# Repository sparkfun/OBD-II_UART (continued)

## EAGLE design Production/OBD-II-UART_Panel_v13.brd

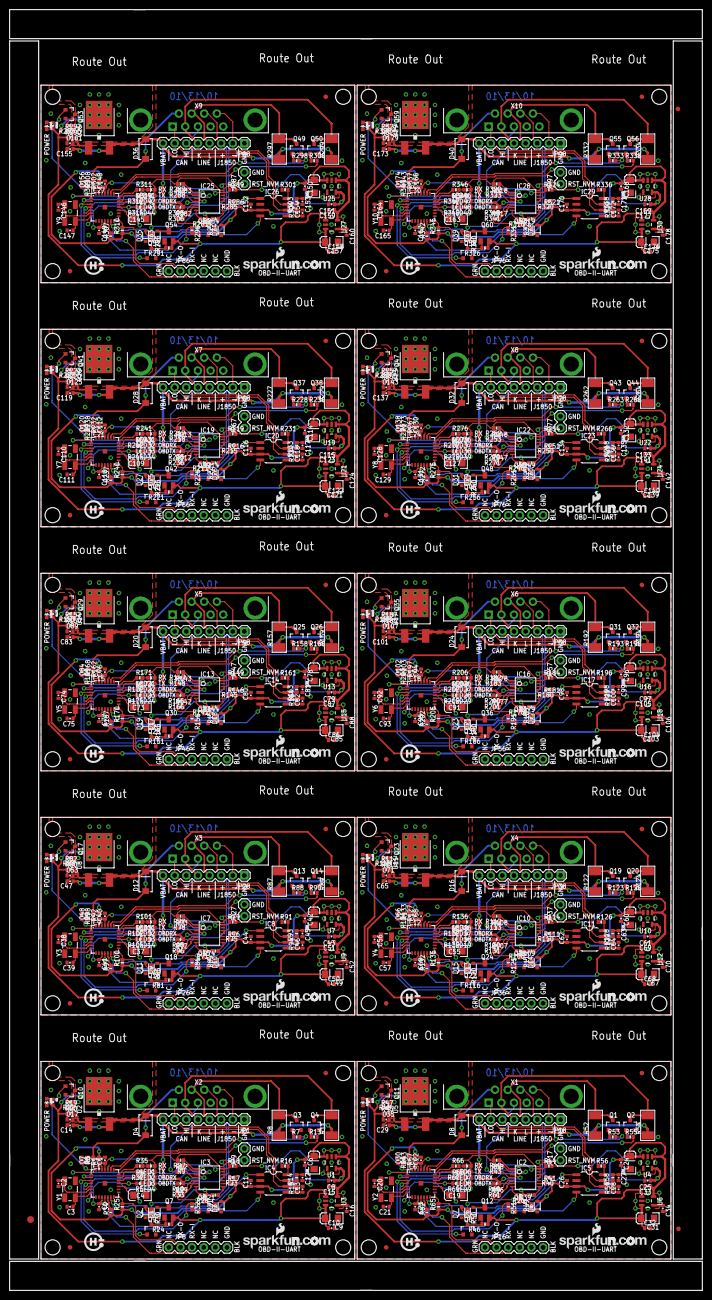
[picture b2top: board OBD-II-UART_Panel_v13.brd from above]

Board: 2 copper layers, 151.4 x 279.9 mm, 873 parts (0 on the bottom side), 570 nets.

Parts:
C1, C5, C6, C11, C17, C22, C23, C24, C26, C35, C40, C41, C42, C44, C53, C58, C59, C60, C62, C71, C76, C77, C78, C80, C89, C94, C95, C96, C98, C107, C112, C113, C114, C116, C125, C130, C131, C132, C134, C143, C148, C149, C150, C152, C161, C166, C167, C168, C170, C179: 1uF; 0402-CAP
C2, C3, C20, C21, C38, C39, C56, C57, C74, C75, C92, C93, C110, C111, C128, C129, C146, C147, C164, C165: 27pF; 0402-CAP
C4, C19, C37, C55, C73, C91, C109, C127, C145, C163: 10uF ESR<=5; EIA3216
C7, C10, C14, C29, C30, C32, C47, C48, C50, C65, C66, C68, C83, C84, C86, C101, C102, C104, C119, C120, C122, C137, C138, C140, C155, C156, C158, C173, C174, C176: 0.1uF; 0402-CAP
C8, C25, C43, C61, C79, C97, C115, C133, C151, C169: 4.7uF; 0402-CAP
C9, C18, C31, C36, C49, C54, C67, C72, C85, C90, C103, C108, C121, C126, C139, C144, C157, C162, C175, C180: 10uF; EIA3216
C12, C13, C27, C28, C45, C46, C63, C64, C81, C82, C99, C100, C117, C118, C135, C136, C153, C154, C171, C172: 560pF; 0402-CAP
C15, C33, C51, C69, C87, C105, C123, C141, C159, C177: 2.2uF; 0402-CAP
C16, C34, C52, C70, C88, C106, C124, C142, C160, C178: 470pF; 0402-CAP
D1, D2, D3, D5, D6, D7, D9, D10, D11, D13, D14, D15, D17, D18, D19, D21, D22, D23, D25, D26, D27, D29, D30, D31, D33, D34, D35, D37, D38, D39: BAS16; SOD-323
D4, D8, D12, D16, D20, D24, D28, D32, D36, D40: MBRA140; SMA-DIODE
E$1: FIDUCIAL-1.5X3
E$5, E$8: FIDUCIAL-1X2
IC1, IC6, IC9, IC12, IC15, IC18, IC21, IC24, IC27, IC30: SCANTOOL; _STN_SCANTOOL_QFN-28-S
IC2, IC3, IC7, IC10, IC13, IC16, IC19, IC22, IC25, IC28: LM339PWR; TSSOP-14
IC4, IC5, IC8, IC11, IC14, IC17, IC20, IC23, IC26, IC29: MCP2551; SO-8
JP1, JP18, JP28, JP38, JP48, JP58, JP68, JP78, JP88, JP98: 1X08
JP2, JP10, JP19, JP20, JP29, JP30, JP39, JP40, JP49, JP50, JP59, JP60, JP69, JP70, JP79, JP80, JP89, JP90, JP99, JP100: FIDUCIAL1X2; FIDUCIAL-1X2
JP3, JP11, JP21, JP31, JP41, JP51, JP61, JP71, JP81, JP91: LOGO-SFENEW; SFE-NEW-WEBLOGO
JP4, JP5, JP6, JP7, JP12, JP13, JP14, JP15, JP22, JP23, JP24, JP25, JP32, JP33, JP34, JP35, JP42, JP43, JP44, JP45, JP52, JP53, JP54, JP55, JP62, JP63, JP64, JP65, JP72, JP73, JP74, JP75, JP82, JP83, JP84, JP85, JP92, JP93, JP94, JP95: STAND-OFF
JP8, JP16, JP26, JP36, JP46, JP56, JP66, JP76, JP86, JP96: DNP; FTDI_BASIC
JP9, JP17, JP27, JP37, JP47, JP57, JP67, JP77, JP87, JP97: DNP; 1X02
LED1, LED3, LED6, LED8, LED11, LED13, LED16, LED18, LED21, LED23, LED26, LED28, LED31, LED33, LED36, LED38, LED41, LED43, LED46, LED48: YELLOW; LED-0603
LED2, LED4, LED5, LED7, LED9, LED10, LED12, LED14, LED15, LED17, LED19, LED20, LED22, LED24, LED25, LED27, LED29, LED30, LED32, LED34, LED35, LED37, LED39, LED40, LED42, LED44, LED45, LED47, LED49, LED50: RED; LED-0603
Q1, Q2, Q3, Q4, Q5, Q8, Q13, Q14, Q15, Q19, Q20, Q21, Q25, Q26, Q27, Q31, Q32, Q33, Q37, Q38, Q39, Q43, Q44, Q45, Q49, Q50, Q51, Q55, Q56, Q57: MMBT2222; SOT23-3
Q6, Q9, Q10, Q11, Q16, Q17, Q22, Q23, Q28, Q29, Q34, Q35, Q40, Q41, Q46, Q47, Q52, Q53, Q58, Q59: BSS138; SOT23-3
Q7, Q12, Q18, Q24, Q30, Q36, Q42, Q48, Q54, Q60: ZXMP6A13FTA; SOT23
R1, R9, R10, R12, R18, R21, R26, R27, R28, R29, R30, R31, R33, R36, R38, R39, R42, R43, R44, R49, R50, R57, R60, R61, R71, R72, R73, R74, R77, R78, R79, R84, R85, R92, R95, R96, R106, R107, R108, R109, R112, R113, R114, R119, R120, R127, R130, R131, R141, R142, R143, R144, R147, R148, R149, R154, R155, R162, R165, R166, R176, R177, R178, R179, R182, R183, R184, R189, R190, R197, R200, R201, R211, R212, R213, R214, R217, R218, R219, R224, R225, R232, R235, R236, R246, R247, R248, R249, R252, R253, R254, R259, R260, R267, R270, R271, R281, R282, R283, R284, R287, R288, R289, R294, R295, R302, R305, R306, R316, R317, R318, R319, R322, R323, R324, R329, R330, R337, R340, R341: 10k; 0402-RES
R2, R7, R13, R32, R51, R53, R55, R70, R86, R88, R90, R105, R121, R123, R125, R140, R156, R158, R160, R175, R191, R193, R195, R210, R226, R228, R230, R245, R261, R263, R265, R280, R296, R298, R300, R315, R331, R333, R335, R350: 1k; 0402-RES
R3, R63, R98, R133, R168, R203, R238, R273, R308, R343: 62K; 0402-RES
R4, R5, R35, R37, R66, R67, R68, R69, R101, R102, R103, R104, R136, R137, R138, R139, R171, R172, R173, R174, R206, R207, R208, R209, R241, R242, R243, R244, R276, R277, R278, R279, R311, R312, R313, R314, R346, R347, R348, R349: 330; 0402-RES
R6, R64, R99, R134, R169, R204, R239, R274, R309, R344: 10K; 0402-RES
R8, R11, R52, R54, R87, R89, R122, R124, R157, R159, R192, R194, R227, R229, R262, R264, R297, R299, R332, R334: 510 0.5W; 2010
R14, R15, R58, R59, R93, R94, R128, R129, R163, R164, R198, R199, R233, R234, R268, R269, R303, R304, R338, R339: 100; 0402-RES
R16, R23, R25, R40, R56, R65, R75, R91, R100, R110, R126, R135, R145, R161, R170, R180, R196, R205, R215, R231, R240, R250, R266, R275, R285, R301, R310, R320, R336, R345: 4.7k; 0402-RES
R17, R41, R76, R111, R146, R181, R216, R251, R286, R321: 1.2k; 0402-RES
R19, R47, R82, R117, R152, R187, R222, R257, R292, R327: 866; 0402-RES
R20, R45, R80, R115, R150, R185, R220, R255, R290, R325: 240; 0402-RES
R22, R48, R83, R118, R153, R188, R223, R258, R293, R328: 374; 0402-RES
R24, R34, R46, R62, R81, R97, R116, R132, R151, R167, R186, R202, R221, R237, R256, R272, R291, R307, R326, R342: 1.5k; 0402-RES
U1, U4, U7, U10, U13, U16, U19, U22, U25, U28: 3.3V; SOT23-5
U2, U5, U8, U11, U14, U17, U20, U23, U26, U29: V_REG_317DPACK; V-REG_DPACK
U3, U6, U9, U12, U15, U18, U21, U24, U27, U30: 5V Reg.; SOT23-5
U$1, U$2, U$3, U$4, U$5, U$6, U$7, U$8, U$9, U$14: OSHW-LOGO
X1, X2, X3, X4, X5, X6, X7, X8, X9, X10: Male DB9; DB9_MALE
Y1, Y2, Y3, Y4, Y5, Y6, Y7, Y8, Y9, Y10: 16MHz; CRYSTAL-SMD-5X3

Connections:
3.3V: C1.1, C5.1, C8.1, IC1.10, IC1.25, LED1.A, LED2.A, LED3.A, LED4.A, R9.2, R18.2, R27.2, U1.5
3.3V1: C22.1, C23.1, C25.1, IC6.10, IC6.25, LED6.A, LED7.A, LED8.A, LED9.A, R42.2, R43.2, R44.2, U4.5
3.3V2: C40.1, C41.1, C43.1, IC9.10, IC9.25, LED11.A, LED12.A, LED13.A, LED14.A, R77.2, R78.2, R79.2, U7.5
3.3V3: C58.1, C59.1, C61.1, IC12.10, IC12.25, LED16.A, LED17.A, LED18.A, LED19.A, R112.2, R113.2, R114.2, U10.5
3.3V4: C76.1, C77.1, C79.1, IC15.10, IC15.25, LED21.A, LED22.A, LED23.A, LED24.A, R147.2, R148.2, R149.2, U13.5
3.3V5: C94.1, C95.1, C97.1, IC18.10, IC18.25, LED26.A, LED27.A, LED28.A, LED29.A, R182.2, R183.2, R184.2, U16.5
3.3V6: C112.1, C113.1, C115.1, IC21.10, IC21.25, LED31.A, LED32.A, LED33.A, LED34.A, R217.2, R218.2, R219.2, U19.5
3.3V7: C130.1, C131.1, C133.1, IC24.10, IC24.25, LED36.A, LED37.A, LED38.A, LED39.A, R252.2, R253.2, R254.2, U22.5
3.3V8: C148.1, C149.1, C151.1, IC27.10, IC27.25, LED41.A, LED42.A, LED43.A, LED44.A, R287.2, R288.2, R289.2, U25.5
3.3V9: C166.1, C167.1, C169.1, IC30.10, IC30.25, LED46.A, LED47.A, LED48.A, LED49.A, R322.2, R323.2, R324.2, U28.5
5V: C6.1, C11.1, C15.1, C18.A, D3.2, IC4.3, R1.2, R17.2, R25.1, R34.1, U1.1, U1.3, U3.5
5V1: C24.1, C26.1, C33.1, C36.A, D6.2, IC5.3, R41.2, R57.2, R62.1, R65.1, U4.1, U4.3, U6.5
5V2: C42.1, C44.1, C51.1, C54.A, D10.2, IC8.3, R76.2, R92.2, R97.1, R100.1, U7.1, U7.3, U9.5
5V3: C60.1, C62.1, C69.1, C72.A, D14.2, IC11.3, R111.2, R127.2, R132.1, R135.1, U10.1, U10.3, U12.5
5V4: C78.1, C80.1, C87.1, C90.A, D18.2, IC14.3, R146.2, R162.2, R167.1, R170.1, U13.1, U13.3, U15.5
5V5: C96.1, C98.1, C105.1, C108.A, D22.2, IC17.3, R181.2, R197.2, R202.1, R205.1, U16.1, U16.3, U18.5
5V6: C114.1, C116.1, C123.1, C126.A, D26.2, IC20.3, R216.2, R232.2, R237.1, R240.1, U19.1, U19.3, U21.5
5V7: C132.1, C134.1, C141.1, C144.A, D30.2, IC23.3, R251.2, R267.2, R272.1, R275.1, U22.1, U22.3, U24.5
5V8: C150.1, C152.1, C159.1, C162.A, D34.2, IC26.3, R286.2, R302.2, R307.1, R310.1, U25.1, U25.3, U27.5
5V9: C168.1, C170.1, C177.1, C180.A, D38.2, IC29.3, R321.2, R337.2, R342.1, R345.1, U28.1, U28.3, U30.5
!ISO_K_TX: IC1.22, R13.2
!ISO_K_TX1: IC6.22, R55.2
!ISO_K_TX2: IC9.22, R90.2
!ISO_K_TX3: IC12.22, R125.2
!ISO_K_TX4: IC15.22, R160.2
!ISO_K_TX5: IC18.22, R195.2
!ISO_K_TX6: IC21.22, R230.2
!ISO_K_TX7: IC24.22, R265.2
!ISO_K_TX8: IC27.22, R300.2
!ISO_K_TX9: IC30.22, R335.2
!ISO_L_TX: IC1.23, R7.2
!ISO_L_TX1: IC6.23, R53.2
!ISO_L_TX2: IC9.23, R88.2
!ISO_L_TX3: IC12.23, R123.2
!ISO_L_TX4: IC15.23, R158.2
!ISO_L_TX5: IC18.23, R193.2
!ISO_L_TX6: IC21.23, R228.2
!ISO_L_TX7: IC24.23, R263.2
!ISO_L_TX8: IC27.23, R298.2
!ISO_L_TX9: IC30.23, R333.2
!ISO_RX: IC1.8, IC3.2, R9.1
!ISO_RX1: IC2.2, IC6.8, R43.1
!ISO_RX2: IC7.2, IC9.8, R78.1
!ISO_RX3: IC10.2, IC12.8, R113.1
!ISO_RX4: IC13.2, IC15.8, R148.1
!ISO_RX5: IC16.2, IC18.8, R183.1
!ISO_RX6: IC19.2, IC21.8, R218.1
!ISO_RX7: IC22.2, IC24.8, R253.1
!ISO_RX8: IC25.2, IC27.8, R288.1
!ISO_RX9: IC28.2, IC30.8, R323.1
!OBD_RX_STATUS!/PGC: IC1.19, R4.1
!OBD_RX_STATUS!/PGC1: IC6.19, R68.1
!OBD_RX_STATUS!/PGC2: IC9.19, R103.1
!OBD_RX_STATUS!/PGC3: IC12.19, R138.1
!OBD_RX_STATUS!/PGC4: IC15.19, R173.1
!OBD_RX_STATUS!/PGC5: IC18.19, R208.1
!OBD_RX_STATUS!/PGC6: IC21.19, R243.1
!OBD_RX_STATUS!/PGC7: IC24.19, R278.1
!OBD_RX_STATUS!/PGC8: IC27.19, R313.1
!OBD_RX_STATUS!/PGC9: IC30.19, R348.1
!VPW_RX: IC1.1, IC3.14, R18.1
!VPW_RX1: IC2.14, IC6.1, R44.1
!VPW_RX2: IC7.14, IC9.1, R79.1
!VPW_RX3: IC10.14, IC12.1, R114.1
!VPW_RX4: IC13.14, IC15.1, R149.1
!VPW_RX5: IC16.14, IC18.1, R184.1
!VPW_RX6: IC19.14, IC21.1, R219.1
!VPW_RX7: IC22.14, IC24.1, R254.1
!VPW_RX8: IC25.14, IC27.1, R289.1
!VPW_RX9: IC28.14, IC30.1, R324.1
BATT_V: C7.1, IC1.27, R3.1, R6.2
BATT_V1: C30.1, IC6.27, R63.1, R64.2
BATT_V2: C48.1, IC9.27, R98.1, R99.2
BATT_V3: C66.1, IC12.27, R133.1, R134.2
BATT_V4: C84.1, IC15.27, R168.1, R169.2
BATT_V5: C102.1, IC18.27, R203.1, R204.2
BATT_V6: C120.1, IC21.27, R238.1, R239.2
BATT_V7: C138.1, IC24.27, R273.1, R274.2
BATT_V8: C156.1, IC27.27, R308.1, R309.2
BATT_V9: C174.1, IC30.27, R343.1, R344.2
CAN_HI: IC4.7, JP1.6, R14.2, X2.3
CAN_HI1: IC5.7, JP18.6, R58.2, X1.3
CAN_HI2: IC8.7, JP28.6, R93.2, X3.3
CAN_HI3: IC11.7, JP38.6, R128.2, X4.3
CAN_HI4: IC14.7, JP48.6, R163.2, X5.3
CAN_HI5: IC17.7, JP58.6, R198.2, X6.3
CAN_HI6: IC20.7, JP68.6, R233.2, X7.3
CAN_HI7: IC23.7, JP78.6, R268.2, X8.3
CAN_HI8: IC26.7, JP88.6, R303.2, X9.3
CAN_HI9: IC29.7, JP98.6, R338.2, X10.3
CAN_LO: IC4.6, JP1.7, R15.2, X2.5
CAN_LO1: IC5.6, JP18.7, R59.2, X1.5
CAN_LO2: IC8.6, JP28.7, R94.2, X3.5
CAN_LO3: IC11.6, JP38.7, R129.2, X4.5
CAN_LO4: IC14.6, JP48.7, R164.2, X5.5
CAN_LO5: IC17.6, JP58.7, R199.2, X6.5
CAN_LO6: IC20.6, JP68.7, R234.2, X7.5
CAN_LO7: IC23.6, JP78.7, R269.2, X8.5
CAN_LO8: IC26.6, JP88.7, R304.2, X9.5
CAN_LO9: IC29.6, JP98.7, R339.2, X10.5
CAN_RX: IC1.11, IC4.4
CAN_RX1: IC5.4, IC6.11
CAN_RX2: IC8.4, IC9.11
CAN_RX3: IC11.4, IC12.11
CAN_RX4: IC14.4, IC15.11
CAN_RX5: IC17.4, IC18.11
CAN_RX6: IC20.4, IC21.11
CAN_RX7: IC23.4, IC24.11
CAN_RX8: IC26.4, IC27.11
CAN_RX9: IC29.4, IC30.11
CAN_TX: IC1.12, IC4.1, R34.2
CAN_TX1: IC5.1, IC6.12, R62.2
CAN_TX2: IC8.1, IC9.12, R97.2
CAN_TX3: IC11.1, IC12.12, R132.2
CAN_TX4: IC14.1, IC15.12, R167.2
CAN_TX5: IC17.1, IC18.12, R202.2
CAN_TX6: IC20.1, IC21.12, R237.2
CAN_TX7: IC23.1, IC24.12, R272.2
CAN_TX8: IC26.1, IC27.12, R307.2
CAN_TX9: IC29.1, IC30.12, R342.2
GND: C1.2, C2.2, C3.2, C4.C, C5.2, C6.2, C7.2, C8.2, C9.C, C10.2, C11.2, C12.2, C13.2, C14.2, C15.2, C16.2, C17.2, C18.C, D2.1, IC1.5, IC1.16, IC1.24, IC1.EXP, IC3.12, IC4.2, JP1.1, JP8.GND, JP9.2, LED5.C, Q3.2, Q4.2, Q8.2, Q9.2, Q10.2, R6.1, R16.1, R22.1, R23.1, R33.2, U1.2, U3.2, X2.1, X2.2
GND1: C19.C, C20.2, C21.2, C22.2, C23.2, C24.2, C25.2, C26.2, C27.2, C28.2, C29.2, C30.2, C31.C, C32.2, C33.2, C34.2, C35.2, C36.C, D7.1, IC2.12, IC5.2, IC6.5, IC6.16, IC6.24, IC6.EXP, JP16.GND, JP17.2, JP18.1, LED10.C, Q1.2, Q2.2, Q5.2, Q6.2, Q11.2, R40.1, R48.1, R56.1, R61.2, R64.1, U4.2, U6.2, X1.1, X1.2
GND2: C37.C, C38.2, C39.2, C40.2, C41.2, C42.2, C43.2, C44.2, C45.2, C46.2, C47.2, C48.2, C49.C, C50.2, C51.2, C52.2, C53.2, C54.C, D11.1, IC7.12, IC8.2, IC9.5, IC9.16, IC9.24, IC9.EXP, JP26.GND, JP27.2, JP28.1, LED15.C, Q13.2, Q14.2, Q15.2, Q16.2, Q17.2, R75.1, R83.1, R91.1, R96.2, R99.1, U7.2, U9.2, X3.1, X3.2
GND3: C55.C, C56.2, C57.2, C58.2, C59.2, C60.2, C61.2, C62.2, C63.2, C64.2, C65.2, C66.2, C67.C, C68.2, C69.2, C70.2, C71.2, C72.C, D15.1, IC10.12, IC11.2, IC12.5, IC12.16, IC12.24, IC12.EXP, JP36.GND, JP37.2, JP38.1, LED20.C, Q19.2, Q20.2, Q21.2, Q22.2, Q23.2, R110.1, R118.1, R126.1, R131.2, R134.1, U10.2, U12.2, X4.1, X4.2
GND4: C73.C, C74.2, C75.2, C76.2, C77.2, C78.2, C79.2, C80.2, C81.2, C82.2, C83.2, C84.2, C85.C, C86.2, C87.2, C88.2, C89.2, C90.C, D19.1, IC13.12, IC14.2, IC15.5, IC15.16, IC15.24, IC15.EXP, JP46.GND, JP47.2, JP48.1, LED25.C, Q25.2, Q26.2, Q27.2, Q28.2, Q29.2, R145.1, R153.1, R161.1, R166.2, R169.1, U13.2, U15.2, X5.1, X5.2
GND5: C91.C, C92.2, C93.2, C94.2, C95.2, C96.2, C97.2, C98.2, C99.2, C100.2, C101.2, C102.2, C103.C, C104.2, C105.2, C106.2, C107.2, C108.C, D23.1, IC16.12, IC17.2, IC18.5, IC18.16, IC18.24, IC18.EXP, JP56.GND, JP57.2, JP58.1, LED30.C, Q31.2, Q32.2, Q33.2, Q34.2, Q35.2, R180.1, R188.1, R196.1, R201.2, R204.1, U16.2, U18.2, X6.1, X6.2
GND6: C109.C, C110.2, C111.2, C112.2, C113.2, C114.2, C115.2, C116.2, C117.2, C118.2, C119.2, C120.2, C121.C, C122.2, C123.2, C124.2, C125.2, C126.C, D27.1, IC19.12, IC20.2, IC21.5, IC21.16, IC21.24, IC21.EXP, JP66.GND, JP67.2, JP68.1, LED35.C, Q37.2, Q38.2, Q39.2, Q40.2, Q41.2, R215.1, R223.1, R231.1, R236.2, R239.1, U19.2, U21.2, X7.1, X7.2
GND7: C127.C, C128.2, C129.2, C130.2, C131.2, C132.2, C133.2, C134.2, C135.2, C136.2, C137.2, C138.2, C139.C, C140.2, C141.2, C142.2, C143.2, C144.C, D31.1, IC22.12, IC23.2, IC24.5, IC24.16, IC24.24, IC24.EXP, JP76.GND, JP77.2, JP78.1, LED40.C, Q43.2, Q44.2, Q45.2, Q46.2, Q47.2, R250.1, R258.1, R266.1, R271.2, R274.1, U22.2, U24.2, X8.1, X8.2
GND8: C145.C, C146.2, C147.2, C148.2, C149.2, C150.2, C151.2, C152.2, C153.2, C154.2, C155.2, C156.2, C157.C, C158.2, C159.2, C160.2, C161.2, C162.C, D35.1, IC25.12, IC26.2, IC27.5, IC27.16, IC27.24, IC27.EXP, JP86.GND, JP87.2, JP88.1, LED45.C, Q49.2, Q50.2, Q51.2, Q52.2, Q53.2, R285.1, R293.1, R301.1, R306.2, R309.1, U25.2, U27.2, X9.1, X9.2
GND9: C163.C, C164.2, C165.2, C166.2, C167.2, C168.2, C169.2, C170.2, C171.2, C172.2, C173.2, C174.2, C175.C, C176.2, C177.2, C178.2, C179.2, C180.C, D39.1, IC28.12, IC29.2, IC30.5, IC30.16, IC30.24, IC30.EXP, JP96.GND, JP97.2, JP98.1, LED50.C, Q55.2, Q56.2, Q57.2, Q58.2, Q59.2, R320.1, R328.1, R336.1, R341.2, R344.1, U28.2, U30.2, X10.1, X10.2
J1850BUS+: D1.1, JP1.3, R21.1, R28.1, R30.1, X2.7
J1850BUS+1: D5.1, JP18.3, R26.1, R39.1, R50.1, X1.7
J1850BUS+2: D9.1, JP28.3, R71.1, R74.1, R85.1, X3.7
J1850BUS+3: D13.1, JP38.3, R106.1, R109.1, R120.1, X4.7
J1850BUS+4: D17.1, JP48.3, R141.1, R144.1, R155.1, X5.7
J1850BUS+5: D21.1, JP58.3, R176.1, R179.1, R190.1, X6.7
J1850BUS+6: D25.1, JP68.3, R211.1, R214.1, R225.1, X7.7
J1850BUS+7: D29.1, JP78.3, R246.1, R249.1, R260.1, X8.7
J1850BUS+8: D33.1, JP88.3, R281.1, R284.1, R295.1, X9.7
J1850BUS+9: D37.1, JP98.3, R316.1, R319.1, R330.1, X10.7
J1850BUS+_TX: IC1.3, Q9.1
J1850BUS+_TX1: IC6.3, Q6.1
J1850BUS+_TX2: IC9.3, Q16.1
J1850BUS+_TX3: IC12.3, Q22.1
J1850BUS+_TX4: IC15.3, Q28.1
J1850BUS+_TX5: IC18.3, Q34.1
J1850BUS+_TX6: IC21.3, Q40.1
J1850BUS+_TX7: IC24.3, Q46.1
J1850BUS+_TX8: IC27.3, Q52.1
J1850BUS+_TX9: IC30.3, Q58.1
J1850BUS-: JP1.2, Q8.3, R29.1, R31.2, X2.6
J1850BUS-1: JP18.2, Q5.3, R36.1, R49.2, X1.6
J1850BUS-2: JP28.2, Q15.3, R72.1, R84.2, X3.6
J1850BUS-3: JP38.2, Q21.3, R107.1, R119.2, X4.6
J1850BUS-4: JP48.2, Q27.3, R142.1, R154.2, X5.6
J1850BUS-5: JP58.2, Q33.3, R177.1, R189.2, X6.6
J1850BUS-6: JP68.2, Q39.3, R212.1, R224.2, X7.6
J1850BUS-7: JP78.2, Q45.3, R247.1, R259.2, X8.6
J1850BUS-8: JP88.2, Q51.3, R282.1, R294.2, X9.6
J1850BUS-9: JP98.2, Q57.3, R317.1, R329.2, X10.6
J1850BUS-_TX: IC1.4, R32.1
J1850BUS-_TX1: IC6.4, R51.1
J1850BUS-_TX2: IC9.4, R86.1
J1850BUS-_TX3: IC12.4, R121.1
J1850BUS-_TX4: IC15.4, R156.1
J1850BUS-_TX5: IC18.4, R191.1
J1850BUS-_TX6: IC21.4, R226.1
J1850BUS-_TX7: IC24.4, R261.1
J1850BUS-_TX8: IC27.4, R296.1
J1850BUS-_TX9: IC30.4, R331.1
K-LINE: JP1.5, Q4.3, R11.2, R12.1, X2.4
K-LINE1: JP18.5, Q2.3, R38.1, R54.2, X1.4
K-LINE2: JP28.5, Q14.3, R73.1, R89.2, X3.4
K-LINE3: JP38.5, Q20.3, R108.1, R124.2, X4.4
K-LINE4: JP48.5, Q26.3, R143.1, R159.2, X5.4
K-LINE5: JP58.5, Q32.3, R178.1, R194.2, X6.4
K-LINE6: JP68.5, Q38.3, R213.1, R229.2, X7.4
K-LINE7: JP78.5, Q44.3, R248.1, R264.2, X8.4
K-LINE8: JP88.5, Q50.3, R283.1, R299.2, X9.4
K-LINE9: JP98.5, Q56.3, R318.1, R334.2, X10.4
L-LINE: JP1.4, Q3.3, R8.2, X2.8
L-LINE1: JP18.4, Q1.3, R52.2, X1.8
L-LINE2: JP28.4, Q13.3, R87.2, X3.8
L-LINE3: JP38.4, Q19.3, R122.2, X4.8
L-LINE4: JP48.4, Q25.3, R157.2, X5.8
L-LINE5: JP58.4, Q31.3, R192.2, X6.8
L-LINE6: JP68.4, Q37.3, R227.2, X7.8
L-LINE7: JP78.4, Q43.3, R262.2, X8.8
L-LINE8: JP88.4, Q49.3, R297.2, X9.8
L-LINE9: JP98.4, Q55.3, R332.2, X10.8
unnamed: IC3.7, R28.2
unnamed: C19.A, IC6.17
unnamed: IC3.6, R29.2
unnamed: Q4.1, R13.1
unnamed: Q3.1, R7.1
unnamed: IC3.5, R10.2, R33.1
unnamed: IC3.8, R21.2
unnamed: R19.2, R20.2, U2.1
unnamed: D1.2, Q7.3
unnamed: C12.1, R14.1
unnamed: IC4.8, R16.2
unnamed: IC3.9, R17.1, R23.2
unnamed: IC3.4, R12.2
unnamed: D3.1, R31.1
unnamed: IC2.7, R26.2
unnamed: IC2.6, R36.2
unnamed: IC2.9, R40.2, R41.1
unnamed: Q7.1, Q9.3, R24.2
unnamed: D6.1, R49.1
unnamed: Q6.3, Q12.1, R46.2
unnamed: Q11.3, R47.1, R48.2
unnamed: Q10.3, R19.1, R22.2
unnamed: D7.2, R50.2
unnamed: D2.2, R30.2
unnamed: Q8.1, R32.2
unnamed: C4.A, IC1.17
unnamed: C13.1, R15.1
unnamed: Q5.1, R51.2
unnamed: Q2.1, R55.1
unnamed: LED3.C, R4.2
unnamed: LED4.C, R5.1
unnamed: LED5.A, R2.1
unnamed: Q1.1, R53.1
unnamed: C16.1, U3.4
unnamed: LED1.C, R35.2
unnamed: LED2.C, R37.1
unnamed: IC5.8, R56.2
unnamed: C27.1, R58.1
unnamed: C28.1, R59.1
unnamed: R45.2, R47.2, U5.1
unnamed: IC2.5, R60.2, R61.1
unnamed: IC2.4, R38.2
unnamed: IC2.8, R39.2
unnamed: D5.2, Q12.3
unnamed: LED6.C, R66.2
unnamed: LED7.C, R67.1
unnamed: LED8.C, R68.2
unnamed: LED9.C, R69.1
unnamed: C34.1, U6.4
unnamed: LED10.A, R70.1
unnamed: C37.A, IC9.17
unnamed: IC7.7, R71.2
unnamed: IC7.6, R72.2
unnamed: IC7.9, R75.2, R76.1
unnamed: D10.1, R84.1
unnamed: Q16.3, Q18.1, R81.2
unnamed: Q17.3, R82.1, R83.2
unnamed: D11.2, R85.2
unnamed: Q15.1, R86.2
unnamed: Q14.1, R90.1
unnamed: Q13.1, R88.1
unnamed: IC8.8, R91.2
unnamed: C45.1, R93.1
unnamed: C46.1, R94.1
unnamed: R80.2, R82.2, U8.1
unnamed: IC7.5, R95.2, R96.1
unnamed: IC7.4, R73.2
unnamed: IC7.8, R74.2
unnamed: D9.2, Q18.3
unnamed: LED11.C, R101.2
unnamed: LED12.C, R102.1
unnamed: LED13.C, R103.2
unnamed: LED14.C, R104.1
unnamed: C52.1, U9.4
unnamed: LED15.A, R105.1
unnamed: C55.A, IC12.17
unnamed: IC10.7, R106.2
unnamed: IC10.6, R107.2
unnamed: IC10.9, R110.2, R111.1
unnamed: D14.1, R119.1
unnamed: Q22.3, Q24.1, R116.2
unnamed: Q23.3, R117.1, R118.2
unnamed: D15.2, R120.2
unnamed: Q21.1, R121.2
unnamed: Q20.1, R125.1
unnamed: Q19.1, R123.1
unnamed: IC11.8, R126.2
unnamed: C63.1, R128.1
unnamed: C64.1, R129.1
unnamed: R115.2, R117.2, U11.1
unnamed: IC10.5, R130.2, R131.1
unnamed: IC10.4, R108.2
unnamed: IC10.8, R109.2
unnamed: D13.2, Q24.3
unnamed: LED16.C, R136.2
unnamed: LED17.C, R137.1
unnamed: LED18.C, R138.2
unnamed: LED19.C, R139.1
unnamed: C70.1, U12.4
unnamed: LED20.A, R140.1
unnamed: C73.A, IC15.17
unnamed: IC13.7, R141.2
unnamed: IC13.6, R142.2
unnamed: IC13.9, R145.2, R146.1
unnamed: D18.1, R154.1
unnamed: Q28.3, Q30.1, R151.2
unnamed: Q29.3, R152.1, R153.2
unnamed: D19.2, R155.2
unnamed: Q27.1, R156.2
unnamed: Q26.1, R160.1
unnamed: Q25.1, R158.1
unnamed: IC14.8, R161.2
unnamed: C81.1, R163.1
unnamed: C82.1, R164.1
unnamed: R150.2, R152.2, U14.1
unnamed: IC13.5, R165.2, R166.1
unnamed: IC13.4, R143.2
unnamed: IC13.8, R144.2
unnamed: D17.2, Q30.3
unnamed: LED21.C, R171.2
unnamed: LED22.C, R172.1
unnamed: LED23.C, R173.2
unnamed: LED24.C, R174.1
unnamed: C88.1, U15.4
unnamed: LED25.A, R175.1
unnamed: C91.A, IC18.17
unnamed: IC16.7, R176.2
unnamed: IC16.6, R177.2
unnamed: IC16.9, R180.2, R181.1
unnamed: D22.1, R189.1
unnamed: Q34.3, Q36.1, R186.2
unnamed: Q35.3, R187.1, R188.2
unnamed: D23.2, R190.2
unnamed: Q33.1, R191.2
unnamed: Q32.1, R195.1
unnamed: Q31.1, R193.1
unnamed: IC17.8, R196.2
unnamed: C99.1, R198.1
unnamed: C100.1, R199.1
unnamed: R185.2, R187.2, U17.1
unnamed: IC16.5, R200.2, R201.1
unnamed: IC16.4, R178.2
unnamed: IC16.8, R179.2
unnamed: D21.2, Q36.3
unnamed: LED26.C, R206.2
unnamed: LED27.C, R207.1
unnamed: LED28.C, R208.2
unnamed: LED29.C, R209.1
unnamed: C106.1, U18.4
unnamed: LED30.A, R210.1
unnamed: C109.A, IC21.17
unnamed: IC19.7, R211.2
unnamed: IC19.6, R212.2
unnamed: IC19.9, R215.2, R216.1
unnamed: D26.1, R224.1
unnamed: Q40.3, Q42.1, R221.2
unnamed: Q41.3, R222.1, R223.2
unnamed: D27.2, R225.2
unnamed: Q39.1, R226.2
unnamed: Q38.1, R230.1
unnamed: Q37.1, R228.1
unnamed: IC20.8, R231.2
unnamed: C117.1, R233.1
unnamed: C118.1, R234.1
unnamed: R220.2, R222.2, U20.1
unnamed: IC19.5, R235.2, R236.1
unnamed: IC19.4, R213.2
unnamed: IC19.8, R214.2
unnamed: D25.2, Q42.3
unnamed: LED31.C, R241.2
unnamed: LED32.C, R242.1
unnamed: LED33.C, R243.2
unnamed: LED34.C, R244.1
unnamed: C124.1, U21.4
unnamed: LED35.A, R245.1
unnamed: C127.A, IC24.17
unnamed: IC22.7, R246.2
unnamed: IC22.6, R247.2
unnamed: IC22.9, R250.2, R251.1
unnamed: D30.1, R259.1
unnamed: Q46.3, Q48.1, R256.2
unnamed: Q47.3, R257.1, R258.2
unnamed: D31.2, R260.2
unnamed: Q45.1, R261.2
unnamed: Q44.1, R265.1
unnamed: Q43.1, R263.1
unnamed: IC23.8, R266.2
unnamed: C135.1, R268.1
unnamed: C136.1, R269.1
unnamed: R255.2, R257.2, U23.1
unnamed: IC22.5, R270.2, R271.1
unnamed: IC22.4, R248.2
unnamed: IC22.8, R249.2
unnamed: D29.2, Q48.3
unnamed: LED36.C, R276.2
unnamed: LED37.C, R277.1
unnamed: LED38.C, R278.2
unnamed: LED39.C, R279.1
unnamed: C142.1, U24.4
unnamed: LED40.A, R280.1
unnamed: C145.A, IC27.17
unnamed: IC25.7, R281.2
unnamed: IC25.6, R282.2
unnamed: IC25.9, R285.2, R286.1
unnamed: D34.1, R294.1
unnamed: Q52.3, Q54.1, R291.2
unnamed: Q53.3, R292.1, R293.2
unnamed: D35.2, R295.2
unnamed: Q51.1, R296.2
unnamed: Q50.1, R300.1
unnamed: Q49.1, R298.1
unnamed: IC26.8, R301.2
unnamed: C153.1, R303.1
unnamed: C154.1, R304.1
unnamed: R290.2, R292.2, U26.1
unnamed: IC25.5, R305.2, R306.1
unnamed: IC25.4, R283.2
unnamed: IC25.8, R284.2
unnamed: D33.2, Q54.3
unnamed: LED41.C, R311.2
unnamed: LED42.C, R312.1
unnamed: LED43.C, R313.2
unnamed: LED44.C, R314.1
unnamed: C160.1, U27.4
unnamed: LED45.A, R315.1
unnamed: C163.A, IC30.17
unnamed: IC28.7, R316.2
unnamed: IC28.6, R317.2
unnamed: IC28.9, R320.2, R321.1
unnamed: D38.1, R329.1
unnamed: Q58.3, Q60.1, R326.2
unnamed: Q59.3, R327.1, R328.2
unnamed: D39.2, R330.2
unnamed: Q57.1, R331.2
unnamed: Q56.1, R335.1
unnamed: Q55.1, R333.1
unnamed: IC29.8, R336.2
unnamed: C171.1, R338.1
unnamed: C172.1, R339.1
unnamed: R325.2, R327.2, U29.1
unnamed: IC28.5, R340.2, R341.1
unnamed: IC28.4, R318.2
unnamed: IC28.8, R319.2
unnamed: D37.2, Q60.3
unnamed: LED46.C, R346.2
unnamed: LED47.C, R347.1
unnamed: LED48.C, R348.2
unnamed: LED49.C, R349.1
unnamed: C178.1, U30.4
unnamed: LED50.A, R350.1
OSC1: C2.1, IC1.6, Y1.3
OSC2: C3.1, IC1.7, Y1.1
OSC3: C20.1, IC6.6, Y2.3
OSC4: C21.1, IC6.7, Y2.1
OSC5: C38.1, IC9.6, Y3.3
OSC6: C39.1, IC9.7, Y3.1
OSC7: C56.1, IC12.6, Y4.3
OSC8: C57.1, IC12.7, Y4.1
OSC9: C74.1, IC15.6, Y5.3
OSC10: C75.1, IC15.7, Y5.1
OSC11: C92.1, IC18.6, Y6.3
OSC12: C93.1, IC18.7, Y6.1
OSC13: C110.1, IC21.6, Y7.3
OSC14: C111.1, IC21.7, Y7.1
OSC15: C128.1, IC24.6, Y8.3
OSC16: C129.1, IC24.7, Y8.1
OSC17: C146.1, IC27.6, Y9.3
OSC18: C147.1, IC27.7, Y9.1
OSC19: C164.1, IC30.6, Y10.3
OSC20: C165.1, IC30.7, Y10.1
PWM/!VPW: IC1.28, Q10.1
PWM/!VPW1: IC6.28, Q11.1
PWM/!VPW2: IC9.28, Q17.1
PWM/!VPW3: IC12.28, Q23.1
PWM/!VPW4: IC15.28, Q29.1
PWM/!VPW5: IC18.28, Q35.1
PWM/!VPW6: IC21.28, Q41.1
PWM/!VPW7: IC24.28, Q47.1
PWM/!VPW8: IC27.28, Q53.1
PWM/!VPW9: IC30.28, Q59.1
PWM_RX: IC1.2, IC3.1, R27.1
PWM_RX1: IC2.1, IC6.2, R42.1
PWM_RX2: IC7.1, IC9.2, R77.1
PWM_RX3: IC10.1, IC12.2, R112.1
PWM_RX4: IC13.1, IC15.2, R147.1
PWM_RX5: IC16.1, IC18.2, R182.1
PWM_RX6: IC19.1, IC21.2, R217.1
PWM_RX7: IC22.1, IC24.2, R252.1
PWM_RX8: IC25.1, IC27.2, R287.1
PWM_RX9: IC28.1, IC30.2, R322.1
RESET: IC1.26, R1.1
RESET1: IC6.26, R57.1
RESET2: IC9.26, R92.1
RESET3: IC12.26, R127.1
RESET4: IC15.26, R162.1
RESET5: IC18.26, R197.1
RESET6: IC21.26, R232.1
RESET7: IC24.26, R267.1
RESET8: IC27.26, R302.1
RESET9: IC30.26, R337.1
RST_NVM: IC1.18, JP9.1, R5.2
RST_NVM1: IC6.18, JP17.1, R69.2
RST_NVM2: IC9.18, JP27.1, R104.2
RST_NVM3: IC12.18, JP37.1, R139.2
RST_NVM4: IC15.18, JP47.1, R174.2
RST_NVM5: IC18.18, JP57.1, R209.2
RST_NVM6: IC21.18, JP67.1, R244.2
RST_NVM7: IC24.18, JP77.1, R279.2
RST_NVM8: IC27.18, JP87.1, R314.2
RST_NVM9: IC30.18, JP97.1, R349.2
RX-I: IC1.13, JP8.TXO
RX-I1: IC6.13, JP16.TXO
RX-I2: IC9.13, JP26.TXO
RX-I3: IC12.13, JP36.TXO
RX-I4: IC15.13, JP46.TXO
RX-I5: IC18.13, JP56.TXO
RX-I6: IC21.13, JP66.TXO
RX-I7: IC24.13, JP76.TXO
RX-I8: IC27.13, JP86.TXO
RX-I9: IC30.13, JP96.TXO
RX-STAT: IC1.21, R35.1
RX-STAT1: IC6.21, R66.1
RX-STAT2: IC9.21, R101.1
RX-STAT3: IC12.21, R136.1
RX-STAT4: IC15.21, R171.1
RX-STAT5: IC18.21, R206.1
RX-STAT6: IC21.21, R241.1
RX-STAT7: IC24.21, R276.1
RX-STAT8: IC27.21, R311.1
RX-STAT9: IC30.21, R346.1
TX-O: IC1.14, JP8.RXI, R25.2
TX-O1: IC6.14, JP16.RXI, R65.2
TX-O2: IC9.14, JP26.RXI, R100.2
TX-O3: IC12.14, JP36.RXI, R135.2
TX-O4: IC15.14, JP46.RXI, R170.2
TX-O5: IC18.14, JP56.RXI, R205.2
TX-O6: IC21.14, JP66.RXI, R240.2
TX-O7: IC24.14, JP76.RXI, R275.2
TX-O8: IC27.14, JP86.RXI, R310.2
TX-O9: IC30.14, JP96.RXI, R345.2
TX-STAT: IC1.20, R37.2
TX-STAT1: IC6.20, R67.2
TX-STAT2: IC9.20, R102.2
TX-STAT3: IC12.20, R137.2
TX-STAT4: IC15.20, R172.2
TX-STAT5: IC18.20, R207.2
TX-STAT6: IC21.20, R242.2
TX-STAT7: IC24.20, R277.2
TX-STAT8: IC27.20, R312.2
TX-STAT9: IC30.20, R347.2
VBAT: C14.1, D4.C, IC3.3, JP1.8, R8.1, R10.1, R11.1, U2.3
VBAT1: C29.1, D8.C, IC2.3, JP18.8, R52.1, R54.1, R60.1, U5.3
VBAT2: C47.1, D12.C, IC7.3, JP28.8, R87.1, R89.1, R95.1, U8.3
VBAT3: C65.1, D16.C, IC10.3, JP38.8, R122.1, R124.1, R130.1, U11.3
VBAT4: C83.1, D20.C, IC13.3, JP48.8, R157.1, R159.1, R165.1, U14.3
VBAT5: C101.1, D24.C, IC16.3, JP58.8, R192.1, R194.1, R200.1, U17.3
VBAT6: C119.1, D28.C, IC19.3, JP68.8, R227.1, R229.1, R235.1, U20.3
VBAT7: C137.1, D32.C, IC22.3, JP78.8, R262.1, R264.1, R270.1, U23.3
VBAT8: C155.1, D36.C, IC25.3, JP88.8, R297.1, R299.1, R305.1, U26.3
VBAT9: C173.1, D40.C, IC28.3, JP98.8, R332.1, R334.1, R340.1, U29.3
VBATT_RAW: D4.A, R3.2, X2.9
VBATT_RAW1: D8.A, R63.2, X1.9
VBATT_RAW2: D12.A, R98.2, X3.9
VBATT_RAW3: D16.A, R133.2, X4.9
VBATT_RAW4: D20.A, R168.2, X5.9
VBATT_RAW5: D24.A, R203.2, X6.9
VBATT_RAW6: D28.A, R238.2, X7.9
VBATT_RAW7: D32.A, R273.2, X8.9
VBATT_RAW8: D36.A, R308.2, X9.9
VBATT_RAW9: D40.A, R343.2, X10.9
VCC: C9.A, C10.1, C17.1, Q7.2, R2.2, R20.1, R24.1, U2.4, U3.1, U3.3
VCC1: C31.A, C32.1, C35.1, Q12.2, R45.1, R46.1, R70.2, U5.4, U6.1, U6.3
VCC2: C49.A, C50.1, C53.1, Q18.2, R80.1, R81.1, R105.2, U8.4, U9.1, U9.3
VCC3: C67.A, C68.1, C71.1, Q24.2, R115.1, R116.1, R140.2, U11.4, U12.1, U12.3
VCC4: C85.A, C86.1, C89.1, Q30.2, R150.1, R151.1, R175.2, U14.4, U15.1, U15.3
VCC5: C103.A, C104.1, C107.1, Q36.2, R185.1, R186.1, R210.2, U17.4, U18.1, U18.3
VCC6: C121.A, C122.1, C125.1, Q42.2, R220.1, R221.1, R245.2, U20.4, U21.1, U21.3
VCC7: C139.A, C140.1, C143.1, Q48.2, R255.1, R256.1, R280.2, U23.4, U24.1, U24.3
VCC8: C157.A, C158.1, C161.1, Q54.2, R290.1, R291.1, R315.2, U26.4, U27.1, U27.3
VCC9: C175.A, C176.1, C179.1, Q60.2, R325.1, R326.1, R350.2, U29.4, U30.1, U30.3

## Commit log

2013-04-25 Adding hardware files, example sketch, and software links.
2013-04-25 Actually adding files in this commit.
2015-10-16 new v13 panel
